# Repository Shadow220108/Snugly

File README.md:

## Snugly 

# What is it?

its a macropad or better known as a hackpad, unlike normal pico or esp32 s3 we used barebones rp2040 which is a well known chip also used in pico, but we wired it bare bones giving us a more better control over our hardware and space (and also cheap)

# why

macropad is REALLY useful when you have a 60% keyboard, also handy when you are bad at learning shortcuts (really handy)

# how does it work

using rp2040, the rust firmware inits and starts the system clock... the basic firmware currently shows total clicks on display and everytime you click a switch the led gets brighter and brighter

# motivation

WE relly loved the hackpad in blueprint and decided to make one of our own but significantly cheaper and better!

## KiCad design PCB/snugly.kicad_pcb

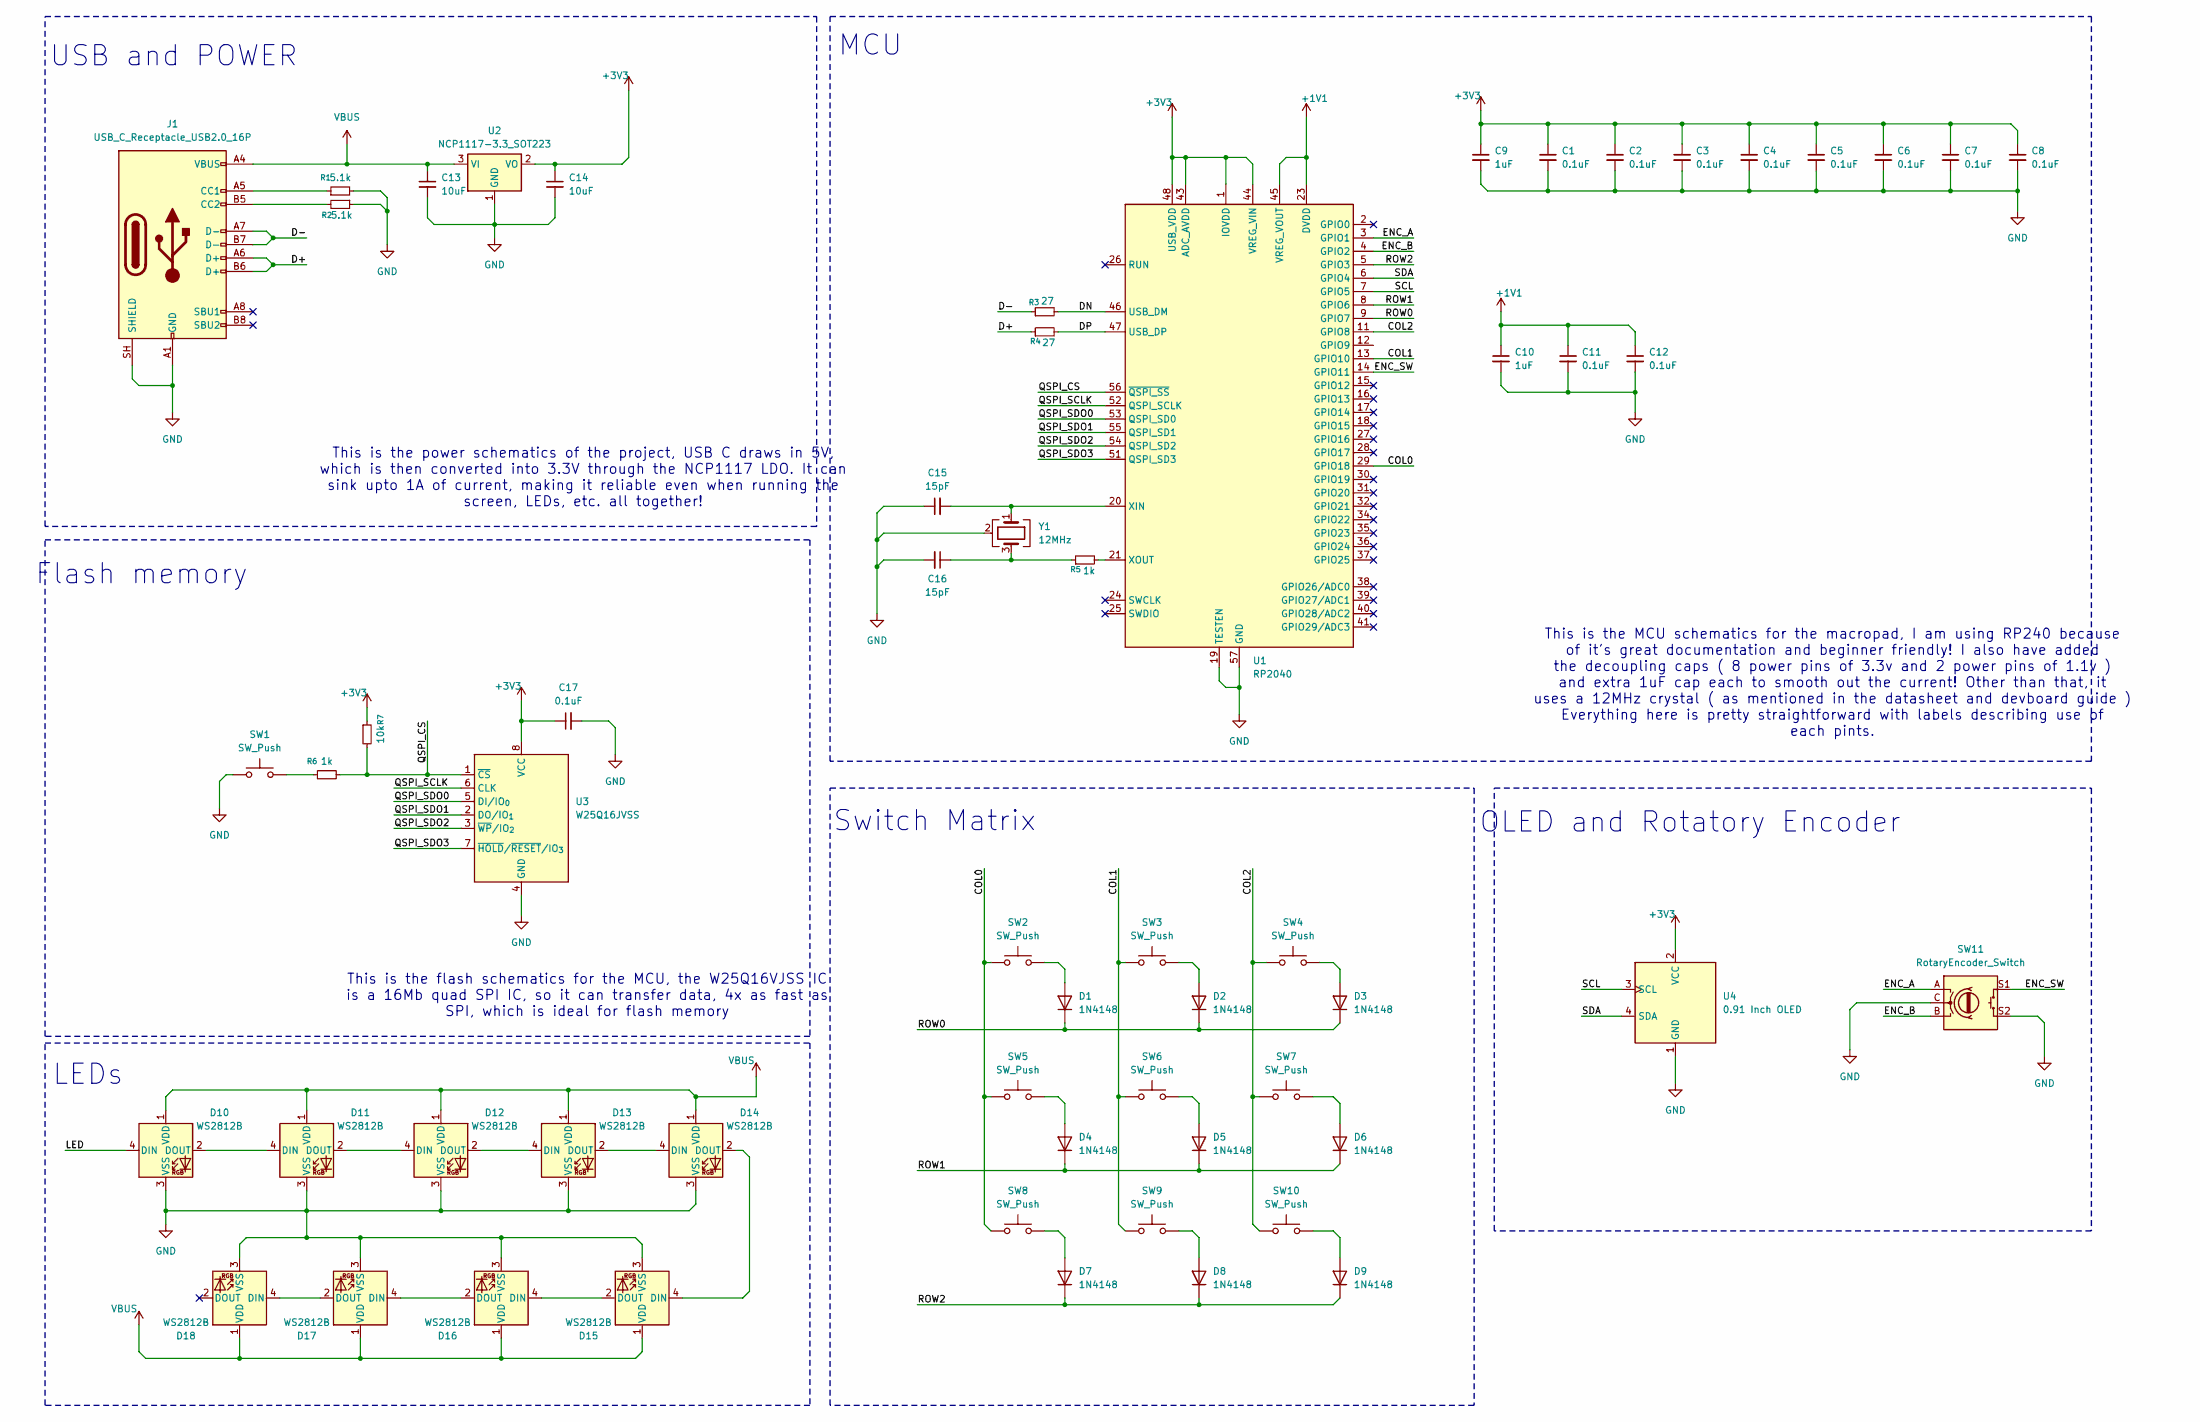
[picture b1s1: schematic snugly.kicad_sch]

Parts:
C1, C2, C3, C4, C5, C6, C7, C8, C11, C12, C17: 0.1uF; C_0402_1005Metric
C9, C10: 1uF; C_0402_1005Metric
C13, C14: 10uF; C_0402_1005Metric
C15, C16: 15pF; C_0402_1005Metric
D1, D2, D3, D4, D5, D6, D7, D8, D9: 1N4148; C_0402_1005Metric
D10, D11, D12, D13, D14, D15, D16, D17, D18: WS2812B; LED_WS2812B_PLCC4_5.0x5.0mm_P3.2mm
J1: USB_C_Receptacle_USB2.0_16P; USB_C_Receptacle_HCTL_HC-TYPE-C-16P-01A
R1, R2: 5.1k; R_0402_1005Metric
R3, R4: 27; R_0402_1005Metric
R5, R6: 1k; R_0402_1005Metric
R7: 10k; R_0402_1005Metric
SW1: SW_Push; SW-SMD_4P-L3.0-W2.6-P1.80-LS3.4-TL
SW2, SW3, SW4, SW5, SW6, SW7, SW8, SW9, SW10: SW_Push; SW_Cherry_MX_1.00u_PCB
SW11: RotaryEncoder_Switch; RotaryEncoder_Alps_EC11E-Switch_Vertical_H20mm
U1: RP2040; QFN-56-1EP_7x7mm_P0.4mm_EP3.2x3.2mm
U2: NCP1117-3.3_SOT223; SOT-223-3_TabPin2
U3: W25Q16JVSS; WSON-8_L6.0-W5.0-P1.27-BL-EP
U4: 0.91 Inch OLED; ER_OLEDM0.91_1x-I2C
Y1: 12MHz; CRYSTAL-SMD_4P-L3.2-W2.5-BL

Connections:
+1V1: C10.1, C11.1, C12.1, U1.23 (DVDD), U1.45 (VREG_VOUT), U1.50 (DVDD)
+3V3: C1.1, C2.1, C3.1, C4.1, C5.1, C6.1, C7.1, C8.1, C9.1, C14.1, C17.1, R7.1, U1.1 (IOVDD), U1.10 (IOVDD), U1.22 (IOVDD), U1.33 (IOVDD), U1.42 (IOVDD), U1.43 (ADC_AVDD), U1.44 (VREG_VIN), U1.48 (USB_VDD), U1.49 (IOVDD), U2.2 (VO), U3.8 (VCC), U4.2 (VCC)
/COL0: SW2.1, SW5.1, SW8.1, U1.29 (GPIO18)
/COL1: SW3.1, SW6.1, SW9.1, U1.13 (GPIO10)
/COL2: SW4.1, SW7.1, SW10.1, U1.11 (GPIO8)
/D+: J1.A6 (D+), J1.B6 (D+), R4.1
/D-: J1.A7 (D-), J1.B7 (D-), R3.1
/DN: R3.2, U1.46 (USB_DM)
/DP: R4.2, U1.47 (USB_DP)
/ENC_A: SW11.A, U1.3 (GPIO1)
/ENC_B: SW11.B, U1.4 (GPIO2)
/ENC_SW: SW11.S1, U1.14 (GPIO11)
/LED: D10.4 (DIN)
/QSPI_CS: R6.2, R7.2, U1.56 (~QSPI_SS), U3.1 (~CS)
/QSPI_SCLK: U1.52 (QSPI_SCLK), U3.6 (CLK)
/QSPI_SDO0: U1.53 (QSPI_SD0), U3.5 (DI/IO_{0})
/QSPI_SDO1: U1.55 (QSPI_SD1), U3.2 (DO/IO_{1})
/QSPI_SDO2: U1.54 (QSPI_SD2), U3.3 (~WP/IO_{2})
/QSPI_SDO3: U1.51 (QSPI_SD3), U3.7 (~HOLD/~RESET/IO_{3})
/ROW0: D1.1 (K), D2.1 (K), D3.1 (K), U1.9 (GPIO7)
/ROW1: D4.1 (K), D5.1 (K), D6.1 (K), U1.8 (GPIO6)
/ROW2: D7.1 (K), D8.1 (K), D9.1 (K), U1.5 (GPIO3)
/SCL: U1.7 (GPIO5), U4.3 (SCL)
/SDA: U1.6 (GPIO4), U4.4 (SDA)
GND: C1.2, C2.2, C3.2, C4.2, C5.2, C6.2, C7.2, C8.2, C9.2, C10.2, C11.2, C12.2, C13.2, C14.2, C15.1, C16.2, C17.2, D10.3 (VSS), D11.3 (VSS), D12.3 (VSS), D13.3 (VSS), D14.3 (VSS), D15.3 (VSS), D16.3 (VSS), D17.3 (VSS), D18.3 (VSS), J1.A1 (GND), J1.A12 (GND), J1.B1 (GND), J1.B12 (GND), J1.SH (SHIELD), R1.2, R2.1, SW1.1, SW11.C, SW11.S2, U1.19 (TESTEN), U1.57 (GND), U2.1 (GND), U3.4 (GND), U4.1 (GND), Y1.2 (G), Y1.4 (G)
unnamed: C16.1, R5.1, Y1.3
unnamed: D1.2 (A), SW2.2
unnamed: D2.2 (A), SW3.2
unnamed: D3.2 (A), SW4.2
unnamed: D4.2 (A), SW5.2
unnamed: D5.2 (A), SW6.2
unnamed: D6.2 (A), SW7.2
unnamed: D7.2 (A), SW8.2
unnamed: D8.2 (A), SW9.2
unnamed: D9.2 (A), SW10.2
unnamed: D10.2 (DOUT), D11.4 (DIN)
unnamed: D11.2 (DOUT), D12.4 (DIN)
unnamed: D12.2 (DOUT), D13.4 (DIN)
unnamed: D13.2 (DOUT), D14.4 (DIN)
unnamed: D14.2 (DOUT), D15.4 (DIN)
unnamed: D15.2 (DOUT), D16.4 (DIN)
unnamed: D16.2 (DOUT), D17.4 (DIN)
unnamed: D17.2 (DOUT), D18.4 (DIN)
unnamed: J1.A5 (CC1), R1.1
unnamed: J1.B5 (CC2), R2.2
unnamed: R6.1, SW1.2
unnamed: C15.2, U1.20 (XIN), Y1.1
unnamed: R5.2, U1.21 (XOUT)
VBUS: C13.1, D10.1 (VDD), D11.1 (VDD), D12.1 (VDD), D13.1 (VDD), D14.1 (VDD), D15.1 (VDD), D16.1 (VDD), D17.1 (VDD), D18.1 (VDD), J1.A4 (VBUS), J1.A9 (VBUS), J1.B4 (VBUS), J1.B9 (VBUS), U2.3 (VI)

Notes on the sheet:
Switch Matrix
USB and POWER
OLED and Rotatory Encoder
This is the power schematics of the project, USB C draws in 5V, which is then converted into 3.3V through the NCP1117 LDO. It can sink upto 1A of current, making it reliable even when running the screen, LEDs, etc. all together!
Flash memory
This is the flash schematics for the MCU, the W25Q16VJSS IC is a 16Mb quad SPI IC, so it can transfer data, 4x as fast as SPI, which is ideal for flash memory
This is the MCU schematics for the macropad, I am using RP240 because of it's great documentation and beginner friendly! I also have added the decoupling caps ( 8 power pins of 3.3v and 2 power pins of 1.1v ) and extra 1uF cap each to smooth out the current! Other than that, it uses a 12MHz crystal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
LEDs
MCU

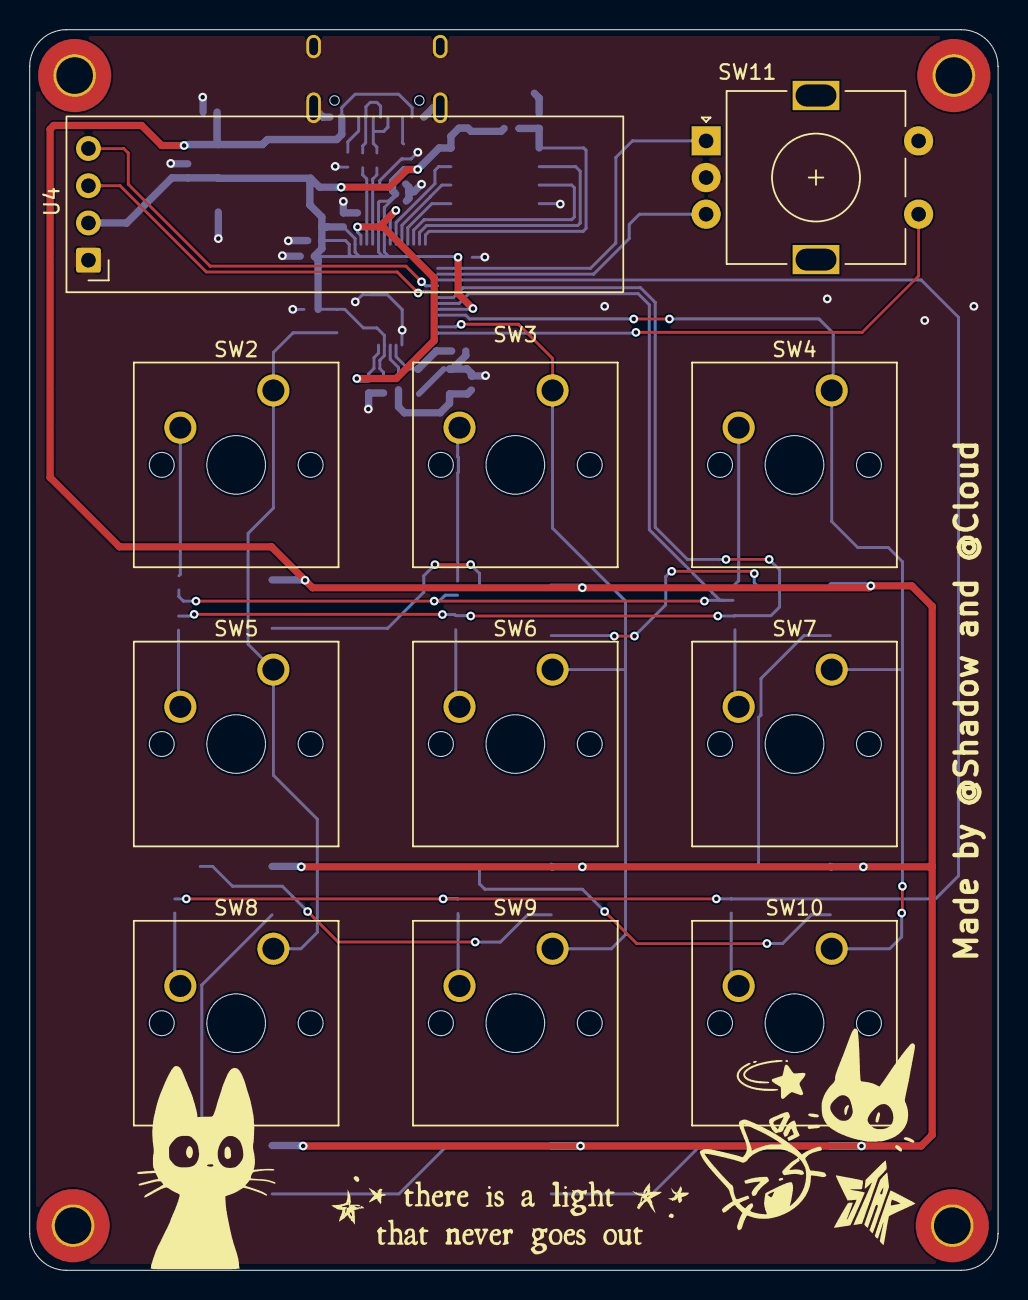
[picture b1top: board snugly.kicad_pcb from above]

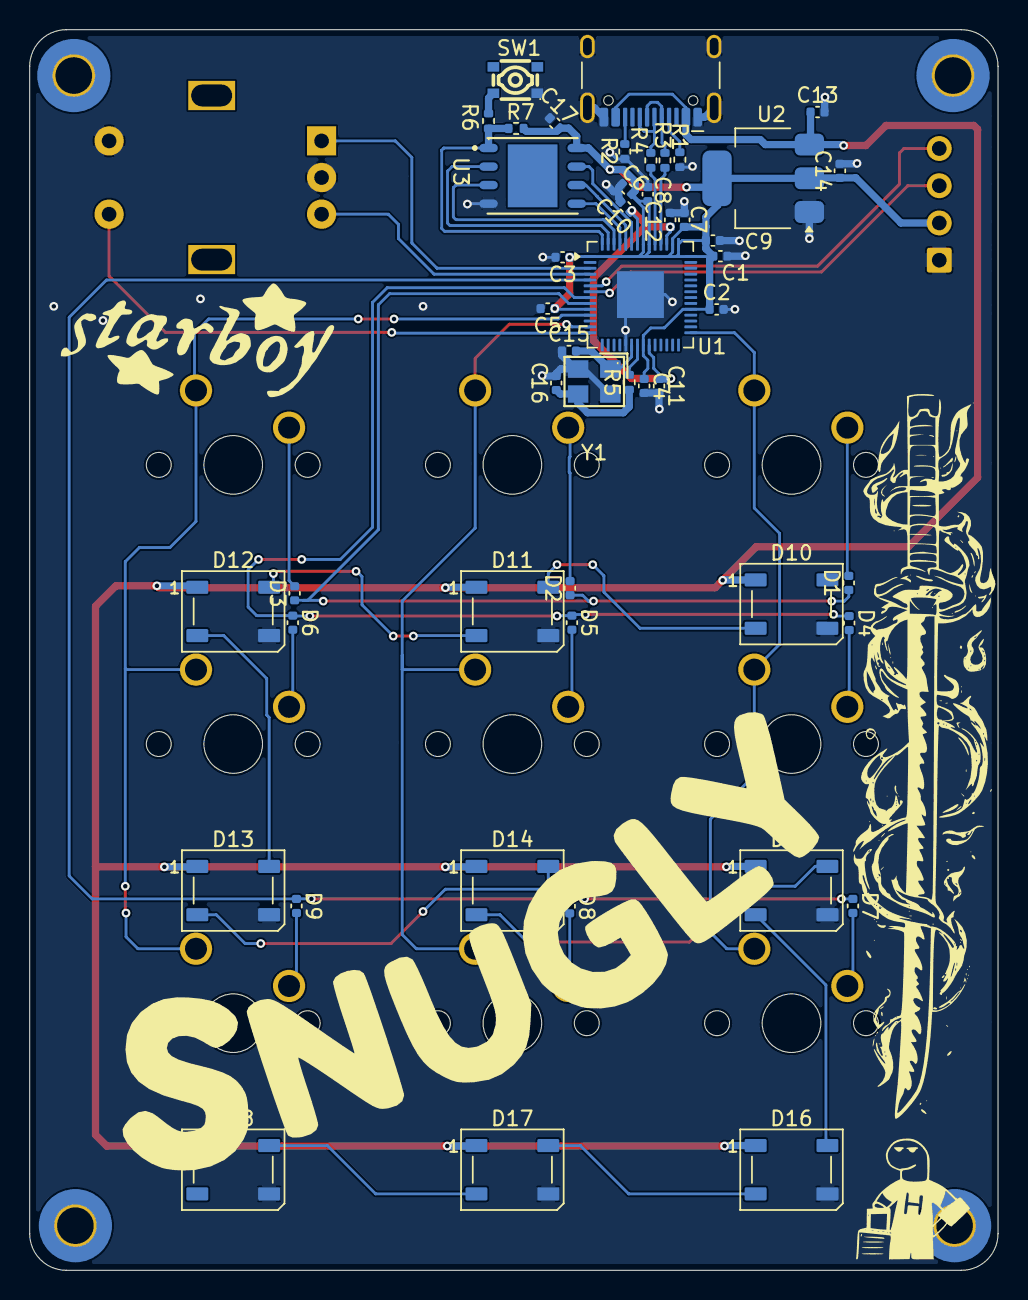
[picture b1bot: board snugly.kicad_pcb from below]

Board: 2 copper layers, 66.1 x 84.7 mm, 59 parts (48 on the bottom side), 48 nets.

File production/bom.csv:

Designator,Footprint,Quantity,Value,LCSC Part #
"C1, C11, C12, C17, C2, C3, C4, C5, C6, C7, C8",0402,11,0.1uF,
"C10, C9",0402,2,1uF,
"C13, C14",0402,2,10uF,
"C15, C16",0402,2,15pF,
"D1, D2, D3, D4, D5, D6, D7, D8, D9",0402,9,1N4148,
"D10, D11, D12, D13, D14, D15, D16, D17, D18",LED_WS2812B_PLCC4_5.0x5.0mm_P3.2mm,9,WS2812B,
J1,USB_C_Receptacle_HCTL_HC-TYPE-C-16P-01A,1,USB_C_Receptacle_USB2.0_16P,
"R1, R2",0402,2,5.1k,
"R3, R4",0402,2,27,
"R5, R6",0402,2,1k,
R7,0402,1,10k,
SW1,SW-SMD_4P-L3.0-W2.6-P1.80-LS3.4-TL,1,SW_Push,C778132
"SW10, SW2, SW3, SW4, SW5, SW6, SW7, SW8, SW9",SW_Cherry_MX_1.00u_PCB,9,SW_Push,
SW11,RotaryEncoder_Alps_EC11E-Switch_Vertical_H20mm,1,RotaryEncoder_Switch,
U1,QFN-56-1EP_7x7mm_P0.4mm_EP3.2x3.2mm,1,RP2040,
U2,SOT-223-3_TabPin2,1,NCP1117-3.3_SOT223,
U3,WSON-8_L6.0-W5.0-P1.27-BL-EP,1,W25Q16JVSS,C2456208
U4,ER_OLEDM0.91_1x-I2C,1,0.91 Inch OLED,
Y1,CRYSTAL-SMD_4P-L3.2-W2.5-BL,1,12MHz,C9002
